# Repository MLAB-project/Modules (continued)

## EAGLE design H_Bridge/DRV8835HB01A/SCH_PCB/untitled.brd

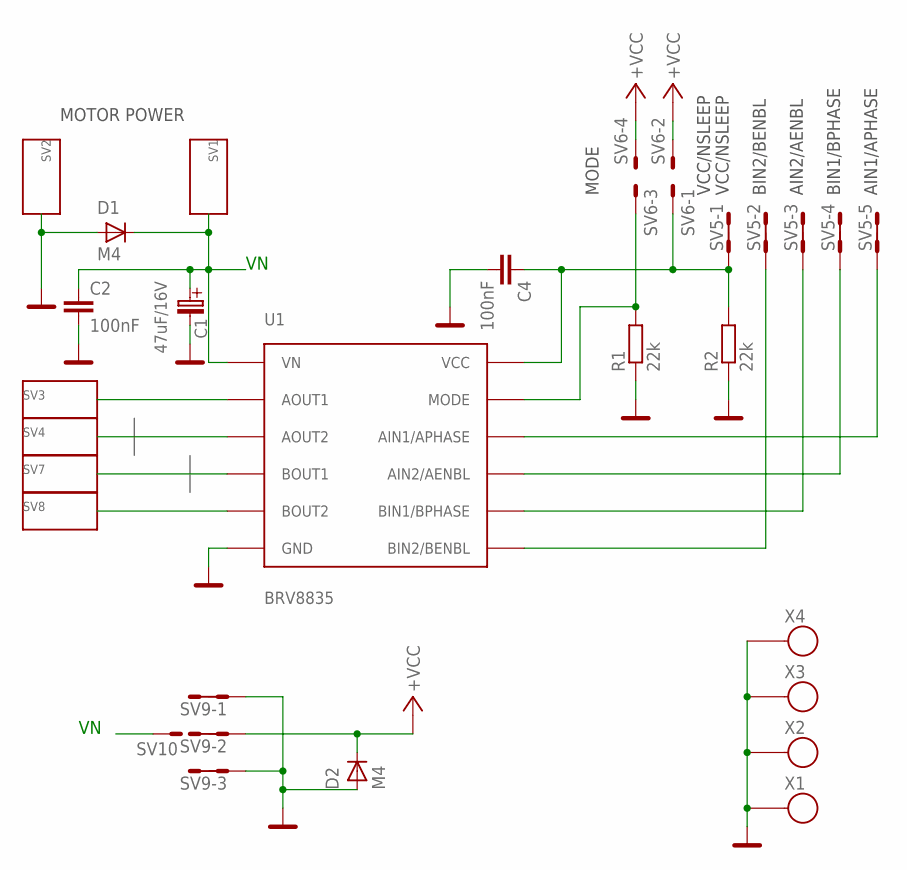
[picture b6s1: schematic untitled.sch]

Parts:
C1: 47uF/16V; C
C2, C4: 100nF; C0805
D1, D2: M4; SMA
R1, R2: 22k; 0805
SV1, SV2, SV3, SV4, SV7, SV8: WAGO256
SV5: MA05-2
SV6: MA02-3; MA02-2
SV9: MA03-2
SV10: MA01-1
U1: BRV8835; WSON
X1, X2, X3, X4: SROUB3M

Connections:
+VCC: D2.K (C), SV6.2, SV6.4, SV9.3, SV9.4
GND: C1.- (C_EL-), C2.2, C4.2, D1.A, D2.A, R1.1, R2.1, SV2.1, SV2.A1, SV9.1, SV9.2, SV9.5, SV9.6, U1.P1 (GND), U1.P2 (GND), U1.P3 (GND), U1.P4 (GND), U1.P5 (GND), U1.P6 (GND), U1.P7 (GND), U1.P8 (GND), U1.P$6 (GND), X1.P$1, X2.P$1, X3.P$1, X4.P$1
unnamed: SV5.5, SV5.6, U1.P$8 (BIN1/BPHASE)
unnamed: SV5.3, SV5.4, U1.P$7 (BIN2/BENBL)
unnamed: R1.2, SV6.3, U1.P$11 (MODE)
unnamed: SV5.7, SV5.8, U1.P$9 (AIN2/AENBL)
unnamed: SV5.9, SV5.10, U1.P$10 (AIN1/APHASE)
unnamed: C4.1, R2.2, SV5.1, SV5.2, SV6.1, U1.P$12 (VCC)
unnamed: SV8.1, SV8.A1, U1.P$5 (BOUT2)
unnamed: SV7.1, SV7.A1, U1.P$4 (BOUT1)
unnamed: SV4.1, SV4.A1, U1.P$3 (AOUT2)
unnamed: SV3.1, SV3.A1, U1.P$2 (AOUT1)
VN: C1.+ (C_EL+), C2.1, D1.K (C), SV1.1, SV1.A1, SV10.1, U1.P$1 (VN)

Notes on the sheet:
VCC/NSLEEP
AIN1/APHASE
AIN2/AENBL
BIN1/BPHASE
BIN2/BENBL
MODE
MOTOR POWER

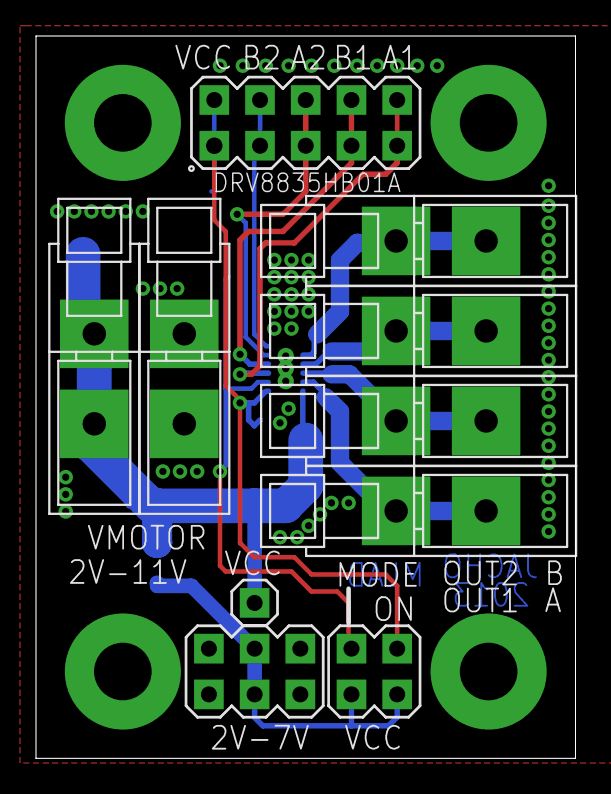
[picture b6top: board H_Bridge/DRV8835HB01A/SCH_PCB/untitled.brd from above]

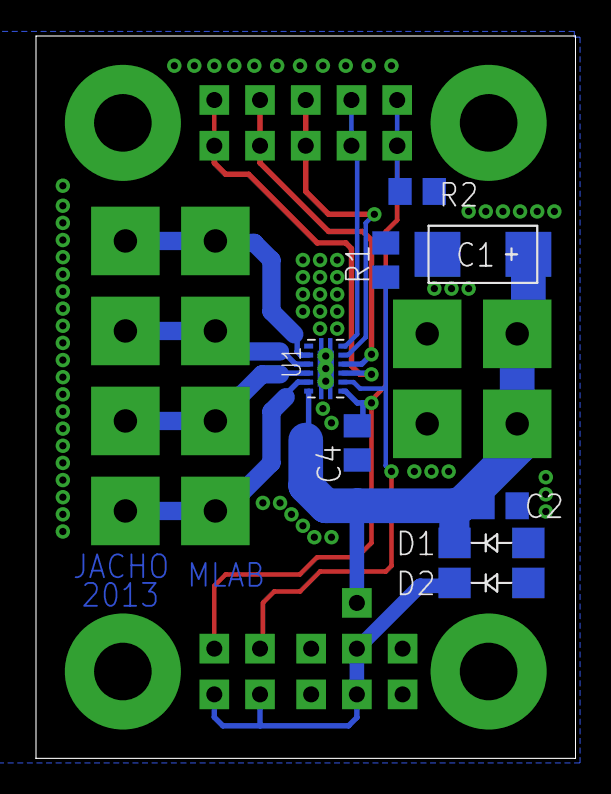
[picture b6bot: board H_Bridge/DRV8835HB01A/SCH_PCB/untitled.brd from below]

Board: 2 copper layers, 30.0 x 40.1 mm, 22 parts (8 on the bottom side), 13 nets.
